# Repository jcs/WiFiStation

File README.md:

# WiFiStation: A WiFi interface to the MailStation

This project is a set of firmware, tools, and hardware specifications for a
board housing an ESP8266 module which talks to a
[Cidco MailStation](https://jcs.org/2019/05/03/mailstation)
over its parallel port.

WiFiStation acts as a modem with an
[`AT` command interface](https://en.wikipedia.org/wiki/Hayes_command_set)
allowing the MailStation to issue `AT` commands to "dial" to telnet addresses
rather than phone numbers.
This allows the MailStation to use software like
[msTERM](https://github.com/jcs/msTERM)
to connect to BBSes over WiFi rather than its internal modem.

All communication between the WiFiStation and the MailStation is also echoed on
the WiFiStation's USB serial interface, so commands can be sent from a host
computer as well.

For the latest documentation for this project, please see
[my WiFiStation site](https://jcs.org/wifistation).

## Hardware Details

An
~~[MCP23017](http://ww1.microchip.com/downloads/en/DeviceDoc/20001952C.pdf)~~
[MCP23S18](http://ww1.microchip.com/downloads/en/devicedoc/22103a.pdf)
connects to an
[Adafruit Feather HUZZAH ESP8266](https://www.adafruit.com/product/2821)
over ~~I2C~~ SPI and has 12 of its GPIO lines (8 data, 2 input status, and 2
output control) routed to pins on a DB25 connector, which plugs into the
MailStation's printer port.

The full
[BOM can be found here.](https://octopart.com/bom-tool/1wY3fCEg)

## Compiling and Flashing esp8266 Firmware

On macOS:

Install Arduino GUI and esp8266 board info per
[these instructions](https://github.com/esp8266/Arduino#installing-with-boards-manager).

```
$ git clone https://github.com/plerup/makeEspArduino
$ git clone https://github.com/jcs/WiFiStation.git
$ cd WiFiStation/esp8266
WiFiStation/esp8266$ make
- Parsing Arduino configuration files ...
- Finding all involved files for the build ...
[...]
WiFiStation/esp8266$ make upload
=== Using upload port: /dev/tty.usbserial-02331261 @ 115200
esptool.py v3.0
Serial port /dev/tty.usbserial-02331261
Connecting....
Chip is ESP8266EX
Features: WiFi
Crystal is 26MHz
[...]
```

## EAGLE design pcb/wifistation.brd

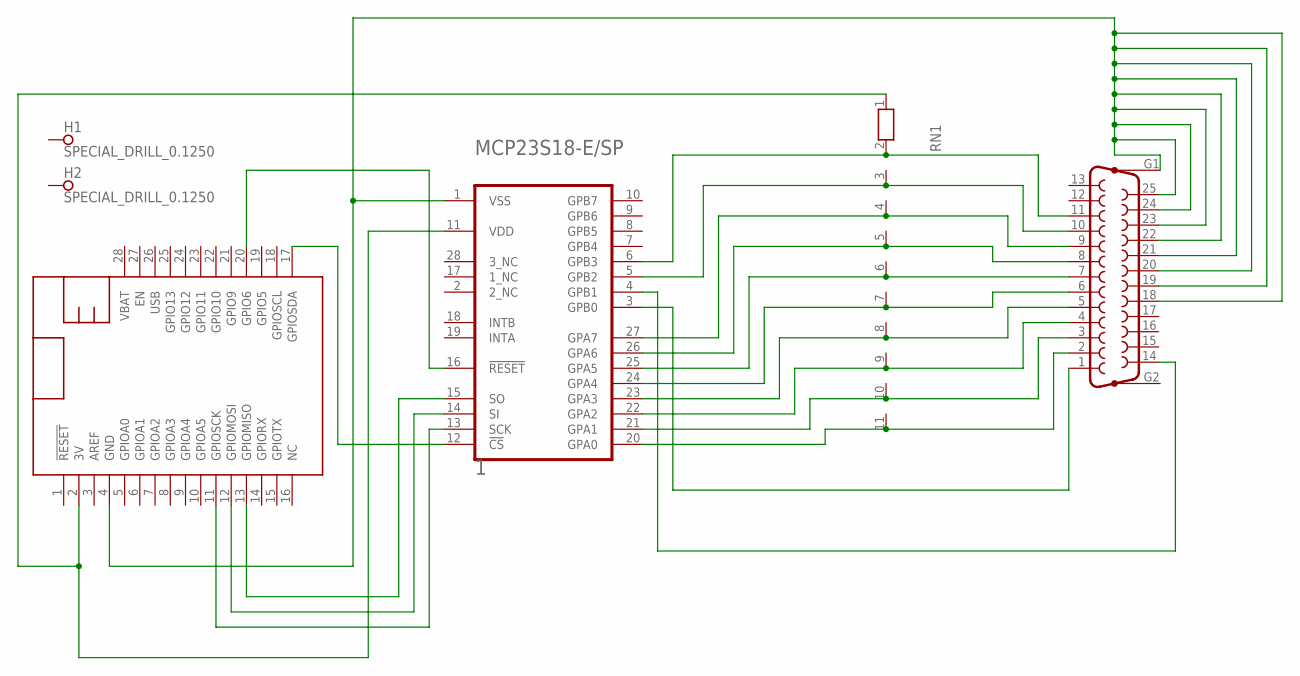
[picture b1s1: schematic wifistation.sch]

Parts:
1: MICROCHIP_MCP23S18-E-SPMICROCHIP_MCP23S18-E-SP_0_0; MICROCHIP_MCP23S18-E-SP_0
DB25: F25HP
FEATHER: FEATHERWING_NODIM_NOHOLES; FEATHERWING_DIM
H1, H2: SPECIAL_DRILL_0.1250; PAD_0.1250
RN1: RN10; RN-11

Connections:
3V: 1.11 (VDD), FEATHER.2 (3V), RN1.1
ACK: 1.5 (GPB2), DB25.10, RN1.3
BUSY: 1.6 (GPB3), DB25.11, RN1.2
DATA0: 1.20 (GPA0), DB25.2, RN1.11
DATA1: 1.21 (GPA1), DB25.3, RN1.10
DATA2: 1.22 (GPA2), DB25.4, RN1.9
DATA3: 1.23 (GPA3), DB25.5, RN1.8
DATA4: 1.24 (GPA4), DB25.6, RN1.7
DATA5: 1.25 (GPA5), DB25.7, RN1.6
DATA6: 1.26 (GPA6), DB25.8, RN1.5
DATA7: 1.27 (GPA7), DB25.9, RN1.4
LINEFEED: 1.4 (GPB1), DB25.14
unnamed: 1.1 (VSS), DB25.18, DB25.19, DB25.20, DB25.21, DB25.22, DB25.23, DB25.24, DB25.25, DB25.G1, FEATHER.4 (GND)
unnamed: 1.15 (SO), FEATHER.13 (GPIOMISO)
unnamed: 1.16 (!RESET!), FEATHER.20 (GPIO6)
unnamed: 1.14 (SI), FEATHER.12 (GPIOMOSI)
unnamed: 1.13 (SCK), FEATHER.11 (GPIOSCK)
unnamed: 1.12 (!CS!), FEATHER.17 (GPIOSDA)
STROBE: 1.3 (GPB0), DB25.1

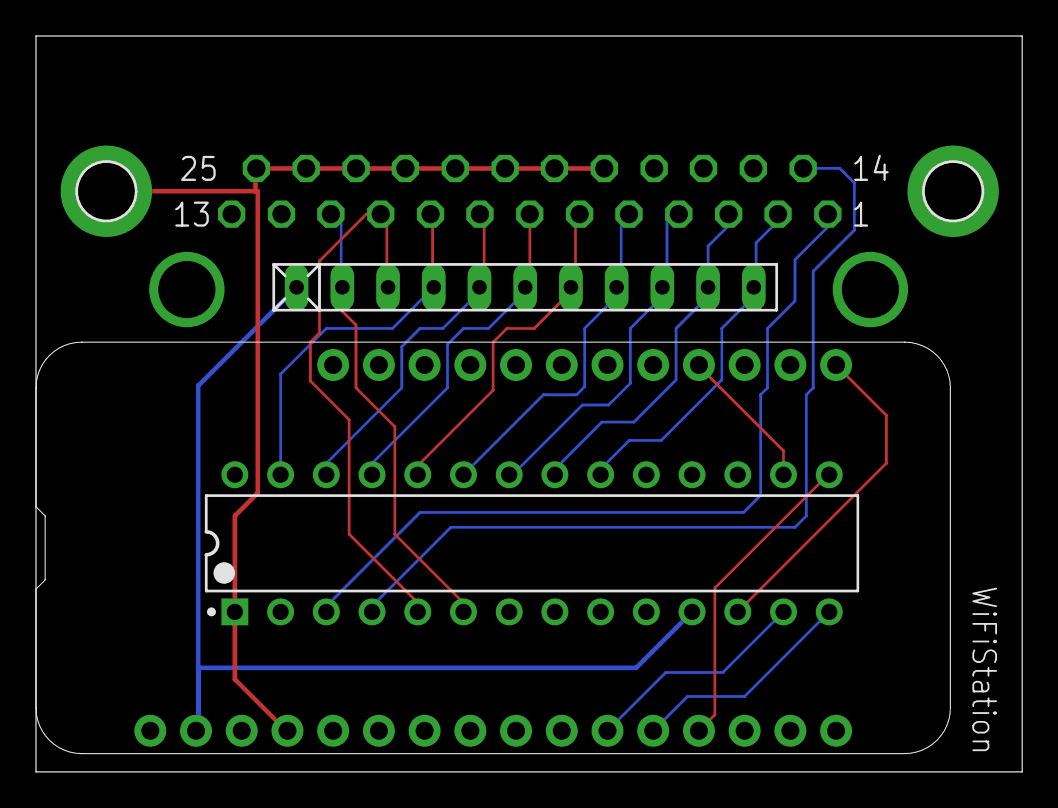
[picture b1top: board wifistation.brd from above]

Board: 2 copper layers, 54.8 x 40.9 mm, 6 parts (0 on the bottom side), 19 nets.

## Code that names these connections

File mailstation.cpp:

#include <Arduino.h>
#include <Wire.h>
#include "Adafruit_MCP23017.h"
#include "mailstation.h"
#include "wifistation.h"

/* these are pins on the MCP23017 */
const int pData0    =  0;
const int pData1    =  1;
const int pData2    =  2;
const int pData3    =  3;
const int pData4    =  4;
const int pData5    =  5;
const int pData6    =  6;
const int pData7    =  7;

const int pBusy     =  8; /* input from lpt pin 1 (strobe) */
const int pAck      =  9; /* input from lpt pin 14 (linefeed) */

const int pLineFeed = 10; /* output to lpt pin 10 (ack) */
const int pStrobe   = 11; /* output to lpt pin 11 (busy) */

Adafruit_MCP23017 mcp;

/* cache data pin direction */
int data_mode;

void
ms_setup(void)
{
	uint16_t v;

	/* use 1.7mhz i2c */
	Wire.setClock(1700000);
	mcp.begin(&Wire);

	/*
	 * check for MCP23017 returning all ones (or most likely, the i2c
	 * library returning all 1s) and flash lights until it's fixed
	 */
	while ((v = mcp.readGPIOAB()) && (v == 0xffff || v == 0xffffffff))
		error_flash();

	led_reset();

	/* data lines will flip between input/output, start in output mode */
	data_mode = OUTPUT;
	for (int i = 0; i <= 7; i++)
		mcp.pinMode(i, OUTPUT);

	/* strobe (control) */
	mcp.pinMode(pStrobe, OUTPUT);
	mcp.digitalWrite(pStrobe, LOW);

	/* linefeed (control) */
	mcp.pinMode(pLineFeed, OUTPUT);
	mcp.digitalWrite(pLineFeed, LOW);

	/* ack (status) */
	mcp.pinMode(pAck, INPUT);
	mcp.pullUp(pAck, LOW);

	/* busy (status) */
	mcp.pinMode(pBusy, INPUT);
	mcp.pullUp(pBusy, LOW);
}

int
ms_read(void)
{
	unsigned long t;
	char c, c2;

	if (mcp.digitalRead(pBusy) != HIGH)
		return -1;

	/* but when both lines are high, something's not right */
	if (mcp.digitalRead(pAck) == HIGH)
		return -1;

	if (data_mode != INPUT) {
		for (int i = 0; i < 8; i++)
			mcp.pinMode(pData0 + i, INPUT);

		data_mode = INPUT;
	}

	mcp.digitalWrite(pLineFeed, HIGH);

	t = millis();
	while (mcp.digitalRead(pBusy) == HIGH) {
		if (millis() - t > 500) {
			mcp.digitalWrite(pLineFeed, LOW);
			error_flash();
			return -1;
		}
		yield();
	}

	c = mcp.readGPIO(0);

	mcp.digitalWrite(pLineFeed, LOW);

	/* invert and reverse data byte */
	c2 = 0;
	for (int i = 0; i < 8; i++)
		if (!(c & (1 << i)))
			c2 |= (1 << i);

	return c2;
}

int
ms_write(char c)
{
	unsigned long t;

	if (data_mode != OUTPUT) {
		for (int i = 0; i < 8; i++)
			mcp.pinMode(pData0 + i, OUTPUT);

		data_mode = OUTPUT;
	}

	mcp.digitalWrite(pStrobe, HIGH);

	t = millis();
	while (mcp.digitalRead(pAck) == LOW) {
		if (millis() - t > 500) {
			mcp.digitalWrite(pStrobe, LOW);
			error_flash();
			return -1;
		}
		ESP.wdtFeed();
	}

	/* write all data lines */
	mcp.writeGPIO(0, c);

	mcp.digitalWrite(pStrobe, LOW);

	t = millis();
	while (mcp.digitalRead(pAck) == HIGH) {
		if (millis() - t > 500)
			return -1;
		ESP.wdtFeed();
	}

	return 0;
}

int
ms_print(String str)
{
	size_t len = str.length();
	int i, ret;

	for (i = 0; i < len; i++) {
		if ((ret = ms_write(str.charAt(i))) != 0)
			return ret;
	}

	return 0;
}

int
ms_print(char *string)
{
	size_t len = strlen(string);
	int i, ret;

	for (i = 0; i < len; i++)
		if ((ret = ms_write(string[i])) != 0)
			return ret;

	return 0;
}

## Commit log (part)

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2021-02-28 Adafruit_MCP23017: implement writeGPIO
2021-02-28 Initial working code of sending and receiving to MailStation
    This uses a new LPT interface to the MailStation that uses all 8
    data lines to simplify reading and writing data, rather than using
    the "tribble" style of transfer in the stock firmware.
    This uses an MCP23017 in i2c mode for all of the GPIO, since there
    aren't enough pins on the ESP8266.
2021-02-28 Use 1.7Mhz I2C clock for faster data transfer
    Still kinda slow though :/
2021-02-28 Start on AT command interface, separate things into separate files
2021-03-02 sendload: The echo and OK might come in two read()s
2021-03-02 Add AT$UPLOAD and host-side sendload program
    sendload is based off of sendload from my mailstation-tools repo but
    modified to only work on the serial interface and use the new
    AT$UPLOAD command.
    Since the TTL connection is so lacking, we rely on the ESP8266
    echoing bytes back to do flow control and limit throughput, which is
    currently still very limited by the MCP23017<->ESP8266 interface.
2021-03-02 ms_write: Go back to writing each pin individually
    Sending more than a few K of data frequently gets corrupted between
    the ESP8266 and the MailStation (all of the data is echoed between
    ESP8266 and host fine). Rather than writing all of the data pins in
    one shot, go back to writing each pin separately. This is obviously
    slower but it seems to be more reliable.
2021-03-02 AT parsing: If errstr is set, print it after "ERROR "
2021-03-02 Rename AT$WATCH to AT$PINS? which WiFi232 already has
2021-03-02 Don't output to serial or MailStation until it talks to us
    Once something is received, consider that channel alive and start
    sending output to it. When ms_write() fails, consider the
    MailStation no longer alive.
2021-03-02 z80: Add new loader program
    This is based on loader.asm from my mailstation-tools repo, but uses
    a custom data transfer routine instead of the firmware's built-in
    "tribble" routines.
    loader.bin clocks in at 116 bytes vs. the original loader's 97.
2021-03-02 Adafruit_MCP23017: Add license headers
    Fetched from
    https://github.com/adafruit/Adafruit-MCP23017-Arduino-Library/blob/master/license.txt
2021-03-02 Add ISC license headers
2021-03-02 sendload: Make serial device a required argument
2021-03-02 sendload: we can't send more than 16k of data, shorten display
2021-03-19 AT$UPLOAD: Only echo every 32 bytes, and echo an XORed sum
    This speeds up things greatly and reduces a ~16k upload time from
    over 4 minutes to about 9 seconds.
    Using an SPI speed of 10Mhz doesn't seem any faster than 5Mhz, so
    stick with 5Mhz for safety.
    This also avoids feeding the ESP watchdog inside the polling loops
    since we timeout after 500ms anyway and the watchdog won't fire
2021-03-19 MCP23S18: Add new driver modeled after Adafruit_MCP23017
2021-03-19 mailstation: No idea why things were reading inverted before
    Simplify this code and we're able to AT$UPLOAD properly again
2021-03-19 mailstation: Add some comments explaining write/read sequence
2021-03-19 exec_cmd: Allocate an extra byte for the null terminator
2021-03-19 mailstation: Allow much more time to read/write, don't start alive
    Some CSI operations are very slow on msTERM. Also consider the
    mailstation dead until it sends us an 'A' or 'a' to avoid reading
    garbage from it.
2021-04-12 mailstation: GPIO_CS moved to pin 4 in board design, reset in loop
    When the MCP23S18 is not responding, be sure to re-initialize it
    each time since we need to be in the right IOCON mode.
2021-04-12 loader: Name this "WSLoader"
    Sorry, you're going to have to key in an extra byte in the hex
    editor.
2021-04-12 Fix \r vs \n handling, allow \r\n but only act on \n
    Also flush serial output after sending \n
2021-04-12 AT$UPLOAD: Simplify output
2021-04-12 sendload: Add helpers for read/write to unify debugging, fix newlines
    We should be sending just \r for commands, not \r\n
2021-04-12 sendload: There will be a final checksum at the end, parse it
2021-04-12 pcb: Add initial version of schematic and board
2021-04-12 pcb: Add revision B, which fixes the pinout of the DB25 connector
    The pinout of the d-sub part in Eagle was backwards from how I was
    using it :(
2021-04-12 pcb: Add revision C which grounds the DB25 mounts and pins 18-25
2021-04-13 ATZ: Use restart instead of reset
2021-04-13 ATI3: Add command to show version
2021-04-13 HTTP: Add HTTP server with file upload interface
    Disabled by default, can be enabled with AT$HTTP=1.
    Since we have to send the file size to WSLoader before sending any
    data and the file upload is streamed to us without the known file
    size, use an intermediate endpoint to measure the file.
    The browser will stream the file to /upload and we'll tally up the
    bytes without sending anything to the MailStation, then we send a
2021-04-14 Loader: Rename to WSLoader, keep binary version in the repo
2021-04-14 AT$SB: Add commands to set and show baud rate
2021-04-14 README: update documentation
2021-04-18 Telnet: If MailStation input starts with \e, buffer for a bit
    This is probably a multi-character key input like an arrow key, so
    buffer it and do telnet.print() with all of the input at once so
    hopefully the remote end gets it all at once.
    Fixes sending arrow keys and Page Up/Down to remote systems that
    don't wait very long to read such input.
2021-04-20 mailstation: Make sure ACK isn't high too
    This can happen when the WiFiStation isn't connected or some other
    bogus condition, so wait until it's low and only BUSY is high
2021-04-20 AT parsing: Handle "A/" with no newline to repeat last command
2021-04-20 AT parsing: Implement +++ with guard time, ATH, and ATO
    When +++ is received when in STATE_TELNET and no further input is
    received for 500ms, switch to STATE_AT.
    ATH will hangup, ATO will switch back to STATE_TELNET.
    Since the Hayes patent #4,549,302 is now expired, we can implement
    this instead of TIES
    https://en.wikipedia.org/wiki/Time_Independent_Escape_Sequence
2021-04-20 mailstation: Add my flashloader adapted for WiFiStation protocol
2021-04-20 sendload: Fix usage printing
2021-04-20 pcb: Add Revision D of board, much smaller now
2021-04-23 README: Link to my documentation site, this will become stale
2021-04-24 enclosure: add final (for now) case design
2021-04-24 LICENSE: add explicit project-wide ISC license
2021-04-24 Build: Add top-level clean target
2021-04-24 ms_setup: Only do error LED flash 10 times
    This way the AT interface can still be entered. Also show
    mailstation_alive status in 'ATI' output.
2021-04-24 enclosure: make tabs 0.1mm longer for a tighter fit
2021-04-25 Build: Add 'release' target to put binaries in release/ for OTA
2021-04-25 Build: Add MD5 to version.txt
2021-04-25 esp8266: Bump firmware to 0.4, now with OTA updating
2021-05-05 telnet_read: Keep reading while telnet object reports available
    There may be bytes to keep reading even after the connection has
    closed.
    Should fix the "Thanks fo" in Tim's video :)
2021-05-16 esp8266: Added bookmark support
2021-05-16 esp8266: Add bookmark support with AT&Z (#1)
2021-05-16 esp8266: Add a static_assert to detect EEPROM_SIZE overflow
2021-05-16 esp8266: Build with -Wall -Wextra
    I don't know why the default would be to suppress all warnings...
2021-05-16 esp8266: Cleanup a bunch of things that -Wall exposed
    Mostly signed/unsigned comparisons, sending const char* to char*
    functions, unused variables, etc.
2021-05-16 esp8266: Minor cleanup of ATI output capitalization
    Clarify that bookmarks are for ATDS
2021-05-16 esp8266: Tag firmware version 0.5
2021-05-16 release: Firmware 0.5
2021-05-20 sendload: Fix AT$UPLOAD echo parsing, improve failure output
    Differentiate between failing to poll, failing to read, and failing
    to compare when checksum fails.
2021-05-20 flashloader: Delay 5 seconds before reading input
    When the CP2104 USB serial chip on the Feather ESP8266 board sees
    the DTR line go low, it causes a reset of the ESP8266. This is
    needed for software (esptool) to be able to put the ESP8266 into its
    bootloader mode.
    Unfortunately this means any serial connection closing causes a
    reboot, which has to reset the MCP23S18, which can cause garbage on
2021-05-20 release: Update flashloader binary
2021-06-21 AT$PINS: Break after ^C
2021-06-21 esp8266: Use new style for collectHeaders
    https://github.com/esp8266/Arduino/commit/47b8947e724b7441d1ad7c7eefdd6fdf691b19c1
2021-06-21 esp8266: Apply default bookmarks on initial setup, too
2021-07-20 release: 0.6
2021-08-30 esp8266: OTA: Fix crash in error handling path
2021-08-30 esp8266: OTA: Keep reading headers while data is available
    The server may have already closed the connection by the time we are
    processing headers, so don't just rely on client.connected().
2021-09-19 Build: Fix path to binary since board changed
2021-09-19 release: 0.7
2021-09-19 telnet: Tweak comment
2022-04-01 esp8266: Only hard-code paths on OpenBSD
    makeEspArduino can find things in their usual places on other
    platforms
2022-08-13 esp8266: Do telnet tracing through syslog directly, fix negotiation
2022-08-13 esp8266: Add syslog support from WiFiPPP, add custom OTA updates
2022-08-13 build: Try to find objcopy on macOS
2022-08-13 README: Link to BOM
    closes #2
2023-06-24 esp8266: AT Handling: Add ATQ and ATE, do proper outputting based on those
    With echo enabled, only print \r after accepting a command, and once
    the command wants to start output, it should print the \n. With ATQ
    set (quiet mode), that \n is not printed since the OK or ERROR is
    not printed.
    Also loop through all command input so chained command sequences
    like "ATEQ1" will be parsed as "ATE0" and "ATQ1".
2023-06-24 esp8266: ATV: Support disabling verbal responses (OK/ERROR)
    Reconfigure ATI responses to be more like other modems, moving WiFi
    scanning to ATI5 and general info to ATI4.
    From WiFiPPP commit eb4842b00be378a43f1610fb8875922af0fd4648
    This is not really needed on WiFiStation but it helps keep code in
    sync.
2023-06-24 esp8266: AT$UPDATE: Allow passing a URL to update from, support non-https
    Also add a 'serve_ota' make target that creates an OTA text file and
    serves it. This should speed up development and allow others to
    update their devices from repos other than mine.
    From WiFiPPP commit d8a0465612ff6c495be3f965de3ca3a4c00cd5bd
2023-06-24 esp8266: OTA: Add tracing
    From WiFiPPP commit 8a3de7fc6ac9e2814e78cc84fd7c671ae803b127
2023-06-24 esp8266: AT: Include leading \r when breaking from +++
    From WiFiPPP commit 646778395fd2082d1a297145bae69e110c167767
2023-06-24 esp8266: OTA: Tweak some debugging output
    From WiFiPPP commit 94cb2999472174716b118448b6a231453610ef8a
2023-06-24 esp8266: AT&W: Force dirty to force commit to do something
    From WiFiPPP commit 47318a7e76ec9b24ed55f9e6ffcc9cd3c19ced96
2023-06-27 esp8266: AT: Don't print newline after ATH
2023-06-27 esp8266: update: Keep reading HTTP body while connected
    This is already done this way in update_http_get_body.
2023-06-27 esp8266: telnet: Send NAWS on IAC DO NAWS
    It may not come through as an SB like TTYPE.
2023-06-27 esp8266: util: Set default baud to 9600
    This is only used when sending TSPEED but it's worth sending a low
    value in case the remote actually uses it.
2023-07-02 enclosure: Add version with no USB port
2023-07-02 esp8266: http: Rename update_http_get_body, it's not getting anything
2023-07-03 esp8266: Disable WiFi.persistent to save flash writes
    Apparently with this on (default) it writes the AP information to
    flash every time WiFi.begin is called. Who knew?
2023-07-03 esp8266: Syslog when we connect to WiFi and show the boot reason
2023-07-03 esp8266: AT: Handle 'ATDT site port' with no colon
2023-07-03 release: 0.9
2023-07-04 esp8266: AT: Remove ATI1-5, move info back to ATI/ATI0
    These came from WiFiPPP which has to emulate a real modem but we
    just need one info screen. Keep AP scanning as a new AT$SCAN
    command.
2023-07-04 esp8266: AT: Add ATDL? and ATDL to show and dial last dialed
2023-07-04 release: 0.9.1
2023-11-08 esp8266: Fix sscanf match for at$upload
2023-11-08 release: 0.9.2
2024-02-26 pcb: Add gerber files I used for the last batch of PCBs
